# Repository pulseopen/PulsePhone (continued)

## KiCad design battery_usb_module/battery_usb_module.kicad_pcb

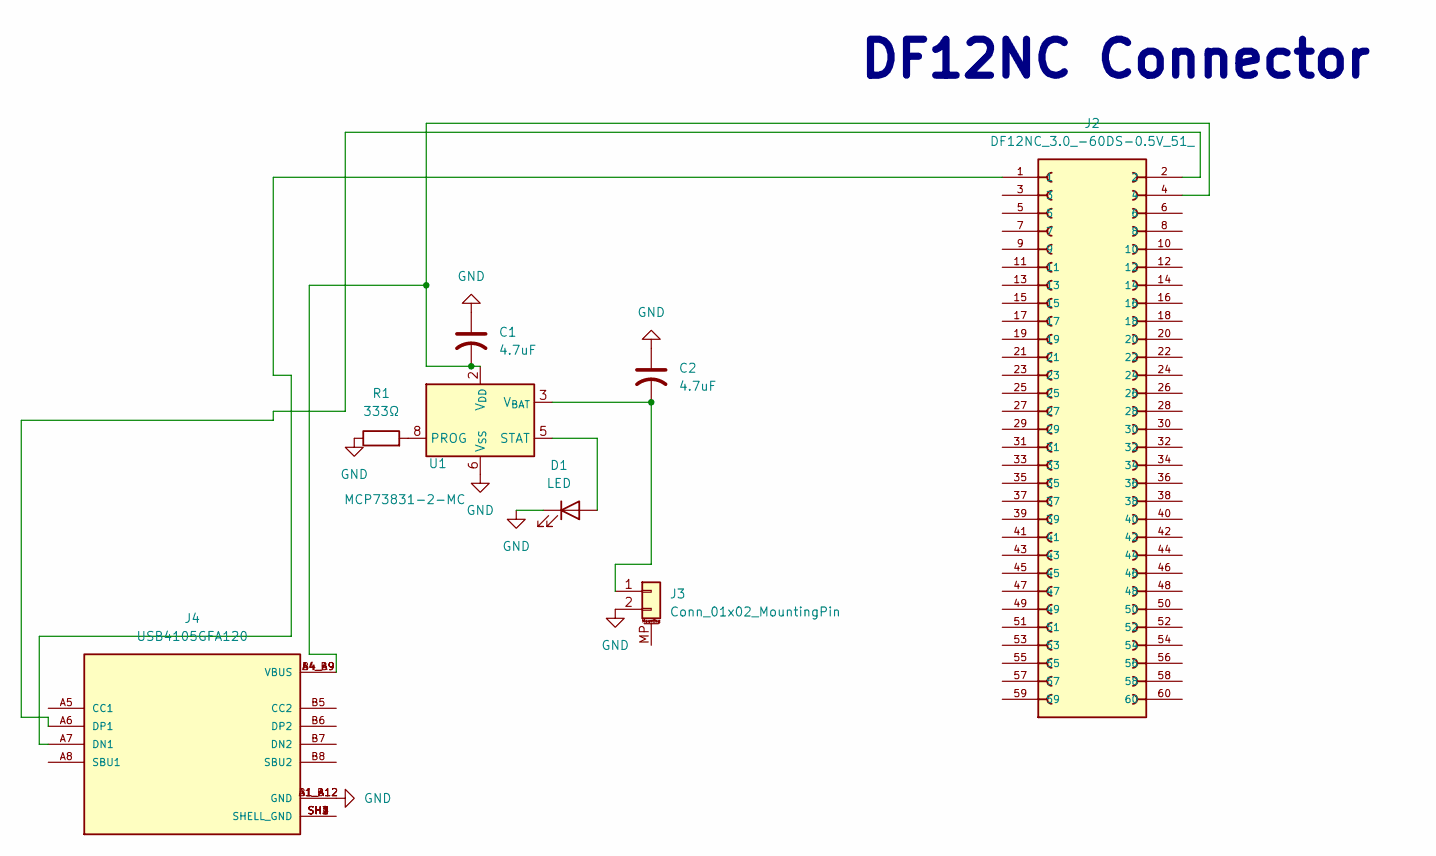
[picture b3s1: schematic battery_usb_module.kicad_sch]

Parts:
C1, C2: 4.7uF; C_0603_1608Metric
D1: LED; LED_0603_1608Metric
J2: DF12NC_3.0_-60DS-0.5V_51_; Hirose_DF12_DF12E3.0-60DP-0.5V_2x30_P0.50mm_Vertical
J3: Conn_01x02_MountingPin; PinHeader_1x02_P1.00mm_Vertical_SMD_Pin1Left
J4: USB4105GFA120; GCT_USB4105GFA120; PARTREV B3
R1: 333Ω; R_0603_1608Metric
U1: MCP73831-2-MC; DFN-8-1EP_3x2mm_P0.5mm_EP1.7x1.4mm

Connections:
GND: C1.1, C2.1, D1.1 (K), J3.2, J4.A1_B12 (GND), J4.B1_A12 (GND), R1.1, U1.6 (V_{SS})
unnamed: C1.2, J2.4, J4.A4_B9 (VBUS), J4.B4_A9 (VBUS), U1.1 (V_{DD}), U1.2 (V_{DD})
unnamed: D1.2 (A), U1.5 (STAT)
unnamed: C2.2, J3.1, U1.3 (V_{BAT}), U1.4 (V_{BAT})
unnamed: J2.1, J4.A7 (DN1)
unnamed: J2.2, J4.A6 (DP1)
unnamed: J4.SH1 (SHELL_GND), J4.SH2 (SHELL_GND), J4.SH3 (SHELL_GND), J4.SH4 (SHELL_GND)
unnamed: R1.2, U1.8 (PROG)

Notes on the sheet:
DF12NC Connector

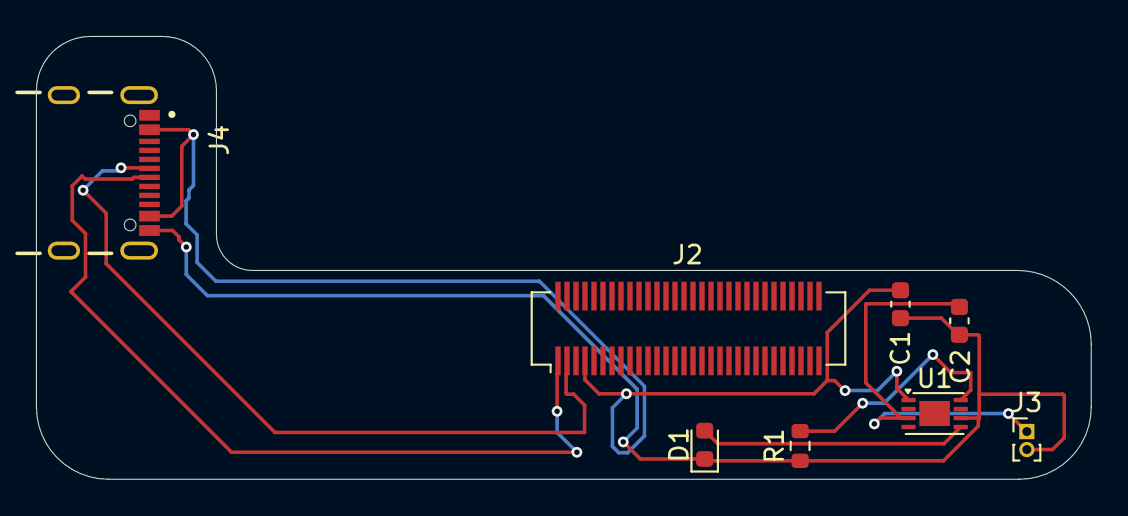
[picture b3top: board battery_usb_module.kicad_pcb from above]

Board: 2 copper layers, 58.6 x 24.6 mm, 8 parts (0 on the bottom side), 8 nets.

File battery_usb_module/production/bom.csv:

Designator,Footprint,Quantity,Value,LCSC Part #
"C1, C2",0603,2,4.7uF,
D1,0603,1,LED,
J2,Hirose_DF12_DF12E3.0-60DP-0.5V_2x30_P0.50mm_Vertical,1,DF12NC_3.0_-60DS-0.5V_51_,
J3,PinHeader_1x02_P1.00mm_Vertical_SMD_Pin1Left,1,Conn_01x02_MountingPin,
J4,GCT_USB4105GFA120,1,USB4105GFA120,
R1,0603,1,333Ω,
U1,DFN-8-1EP_3x2mm_P0.5mm_EP1.7x1.4mm,1,MCP73831-2-MC,

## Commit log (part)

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2025-10-04 Connections for Main Board (WIP)
2025-10-05 Battery Charger Wiring (WIP)
2025-10-05 PCB layout for battery/usb module
2025-10-06 PCB Edge cuts and layout
2025-10-06 Logo edit on main pcb
2025-10-10 Fixed vias and power planes
    Power planes on layers in1-cu and in4-cu where not added and configured, and vias where not going to correct layers.
2025-10-24 Routed battery module pcb
    Completed routing for the battery module section of the modular phone PCB.
    This update connects the battery modules to the main power bus and control lines,
    ensuring proper power distribution and modular interchangeability.
2025-10-24 Removed uneccesary stiffiner labels on user drawings
    Stiffiner labels not necesarry since the idea of the battery module being a flex pcb got scrapped
2025-10-24 Add project reminder for battery connections
    Added a reminder for changing battery connection positions.
2025-10-24 Update project reminder in README
    Adjusted battery module PCB size for case and main PCB.
2025-10-24 Fixed some wrong routing and added missed routing
2025-10-24 Made MIPI-DSI connections on main board
2025-10-24 Fixed text misplacements in front and back silkscreen
2025-10-26 Move connector in battery module ,new usb-c footprint and symbol in pcb and schematic, fixed wrong capacitor values, and redid some wiring on battery module
2025-10-26 Change pin headers on battery usb module to throughhole
2025-10-30 General Changes (Nothing Big)
2025-10-30 Add pulsephone logo to assets
2025-11-06 change branding on main board
2025-11-09 added display folder
2025-11-12 removed inner layers (blind vias are very expensive)
2025-11-12 replaced all power connections with copper pads and started drawing traces to them.
2025-12-04 make new branch and start editing main board schematics
2025-12-12 Add more smoothing caps
2025-12-12 Change README
2025-12-24 Refactor the main board design
    Mainboard is now one big pcb which is the shape and size of the phone. Modules will now attach on top of main board
2026-01-08 Add in new, researched PMICs
2026-01-20 Work on completing schematics and starting pcb design
2026-01-21 Add charging IC and USB-C to schematic and PCB
    Next step is to review PCB layout and start drawing traces
2026-01-28 High speed display traces.
2026-02-24 Finished main_board pcb, and added branding
    The next thing is to start on module development
2026-02-24 pcb: remove backup archives and reposition board logo
2026-02-25 pcb: update board design and related project files
2026-02-25 pcb: update board layout and routing
2026-02-25 Start work on display module schematic.
    Note for later: fix main board PCB, since upon inspection the board has some faults
2026-02-25 Start work on display module schematic.
    NOTE: rework main board PCB, since upon inspection it has multiple faults
2026-02-26 Redo PCB Routing, and added extra features
2026-02-26 finish display module schematic
2026-02-27 Finish Display module.
    The display module is basically an adapter with no fancy features, I choose to do this so pulsephone is compatible with ALL mipi displays since different manufacturers have different pinouts and stan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
2026-02-27 Revamp README.md
2026-02-27 Add .gitignore file to ignore .DS_Store files
2026-02-27 start audio module development with schematic placements
2026-03-01 add extra ground pins to high speed MIPI LANES for reduction of signal coupling.
2026-03-01 rewire traces for new connector scheme
2026-03-01 fix the interrupted gnd plane by moving to 4 layers and adding gnd zones.
2026-03-01 moved to a 4layer pcb with gnd zones to mitigate interrupted gnd plane.
2026-03-01 test
2026-03-01 fix some errors
2026-03-01 remove battery switch
2026-03-01 add sd card slot. also add rst and onoff buttons
2026-03-01 concetrate center of mass ontop of display DF40c
2026-03-01 more smoothing caps, and making sure board is compliant with CompuLab Standards
2026-03-02 fix PCB design errors, and fix power LED circuitry.
2026-03-03 git stuff
2026-03-07 small fixes/I don't remember what I did
2026-03-09 add 3.7v regulator to VBAT for a stable vbat voltage.
2026-03-11 fixes
2026-03-19 footprint size adjustments for better part compatibility when ordering
2026-03-19 initial commit to new rev2 work
2026-04-03 final review change (board was ordered, prod ready verSion)
2026-06-04 restart project for summer, misc changes
2026-06-04 Rev2: fix LBEE5KL1YN power pins, SR_VLX inductor, Y1 LPO_IN wiring, DRC constraints
2026-06-04 Rev2: GND copper pour, reroute, power trace widths
2026-06-04 Rev2: new and improved README
2026-06-04 new WIP mod port (new connector for additional modules to further modify the phone
2026-06-05 new modport addition to pcb -- 3 unconnected pins, WIP
2026-06-15 finish wiring, 3 unconnected -> 0 unconnected
2026-06-15 silkscreen adjustments
2026-06-15 minor tweaks
2026-06-16 add power good leds to 5v and 3v3.
2026-06-18 zone fills
